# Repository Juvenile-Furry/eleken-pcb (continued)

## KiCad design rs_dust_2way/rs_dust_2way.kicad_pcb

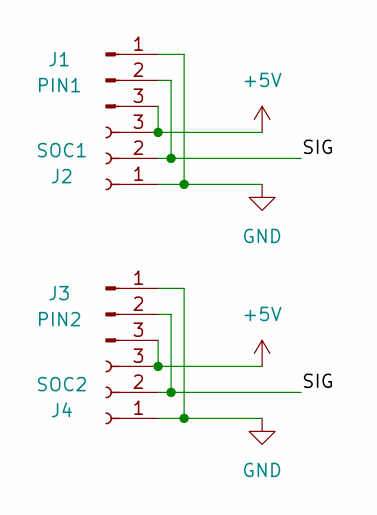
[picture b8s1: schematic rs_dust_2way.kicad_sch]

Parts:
J1: PIN1; PinHeader_1x03_P2.54mm_Horizontal
J2: SOC1; PinSocket_1x03_P2.54mm_Horizontal
J3: PIN2; PinHeader_1x03_P2.54mm_Horizontal
J4: SOC2; PinSocket_1x03_P2.54mm_Horizontal

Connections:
+5V: J1.3, J2.3, J3.3, J4.3
/SIG: J1.2, J2.2, J3.2, J4.2
GND: J1.1, J2.1, J3.1, J4.1

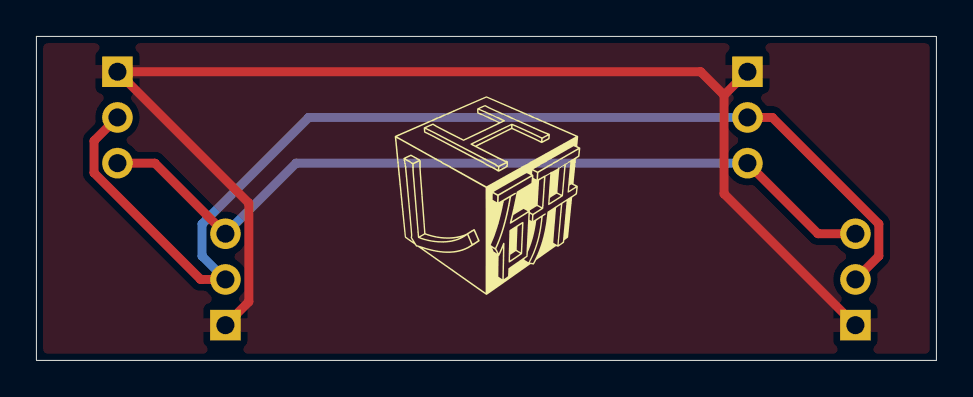
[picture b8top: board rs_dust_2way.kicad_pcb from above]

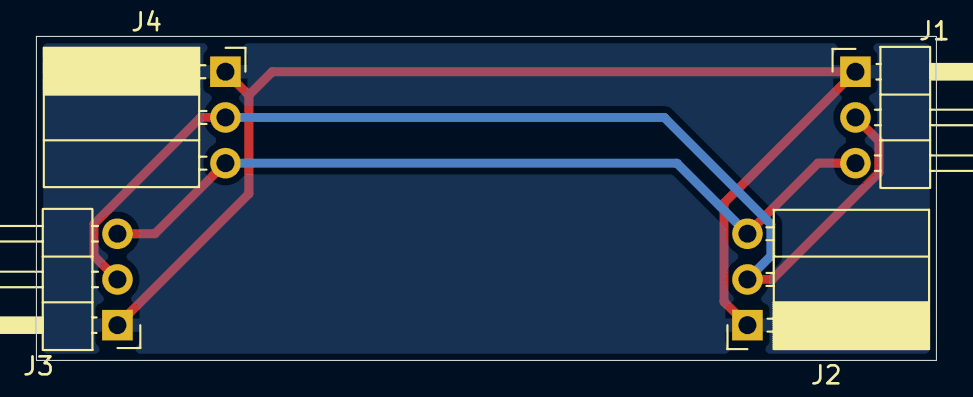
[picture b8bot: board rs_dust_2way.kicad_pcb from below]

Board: 2 copper layers, 50.0 x 18.0 mm, 4 parts (4 on the bottom side), 3 nets.

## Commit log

2026-05-24 retry
2026-05-25 correction
2026-06-05 fixed_lever
2026-06-05 fixed_gitignore
2026-06-06 feat: add rs_note
2026-06-06 aoaoaoaoaoaoaoao_turaku_kibishii_roudou
2026-06-08 fixed_sensor
2026-06-08 fixed_sensor_2
2026-06-09 fixed_torch
